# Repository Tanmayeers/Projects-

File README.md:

-----Welcome to my repository-----

About me
I am a Master's student in Embedded Systems Engineering with a strong passion for hardware design and electronics. These personal projects were created as part of my self-directed learning process to gain practical experience and refine my skills in PCB design and embedded systems development.

All the porjects are created using KiCad 8

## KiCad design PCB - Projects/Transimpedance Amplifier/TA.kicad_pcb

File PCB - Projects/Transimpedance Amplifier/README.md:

Transimpedance Amplifier with Photodiodes

Specifications:
1. Operting Voltage: 9V
2. Operating Current: 200mA
3. Output Voltage Swing: 6.5V
4. 3dB - Bandwidth: 100 ± 10 Hz
5. Noise: 5.406mVrms

Components used:
1. Double operational amplifier - LMC 6482 N
2. Precision Virtual Ground - TLE 2425
3. Photodiodes: SFH 229, BPW 21
4. 9V-Battery, Connectors, R, C

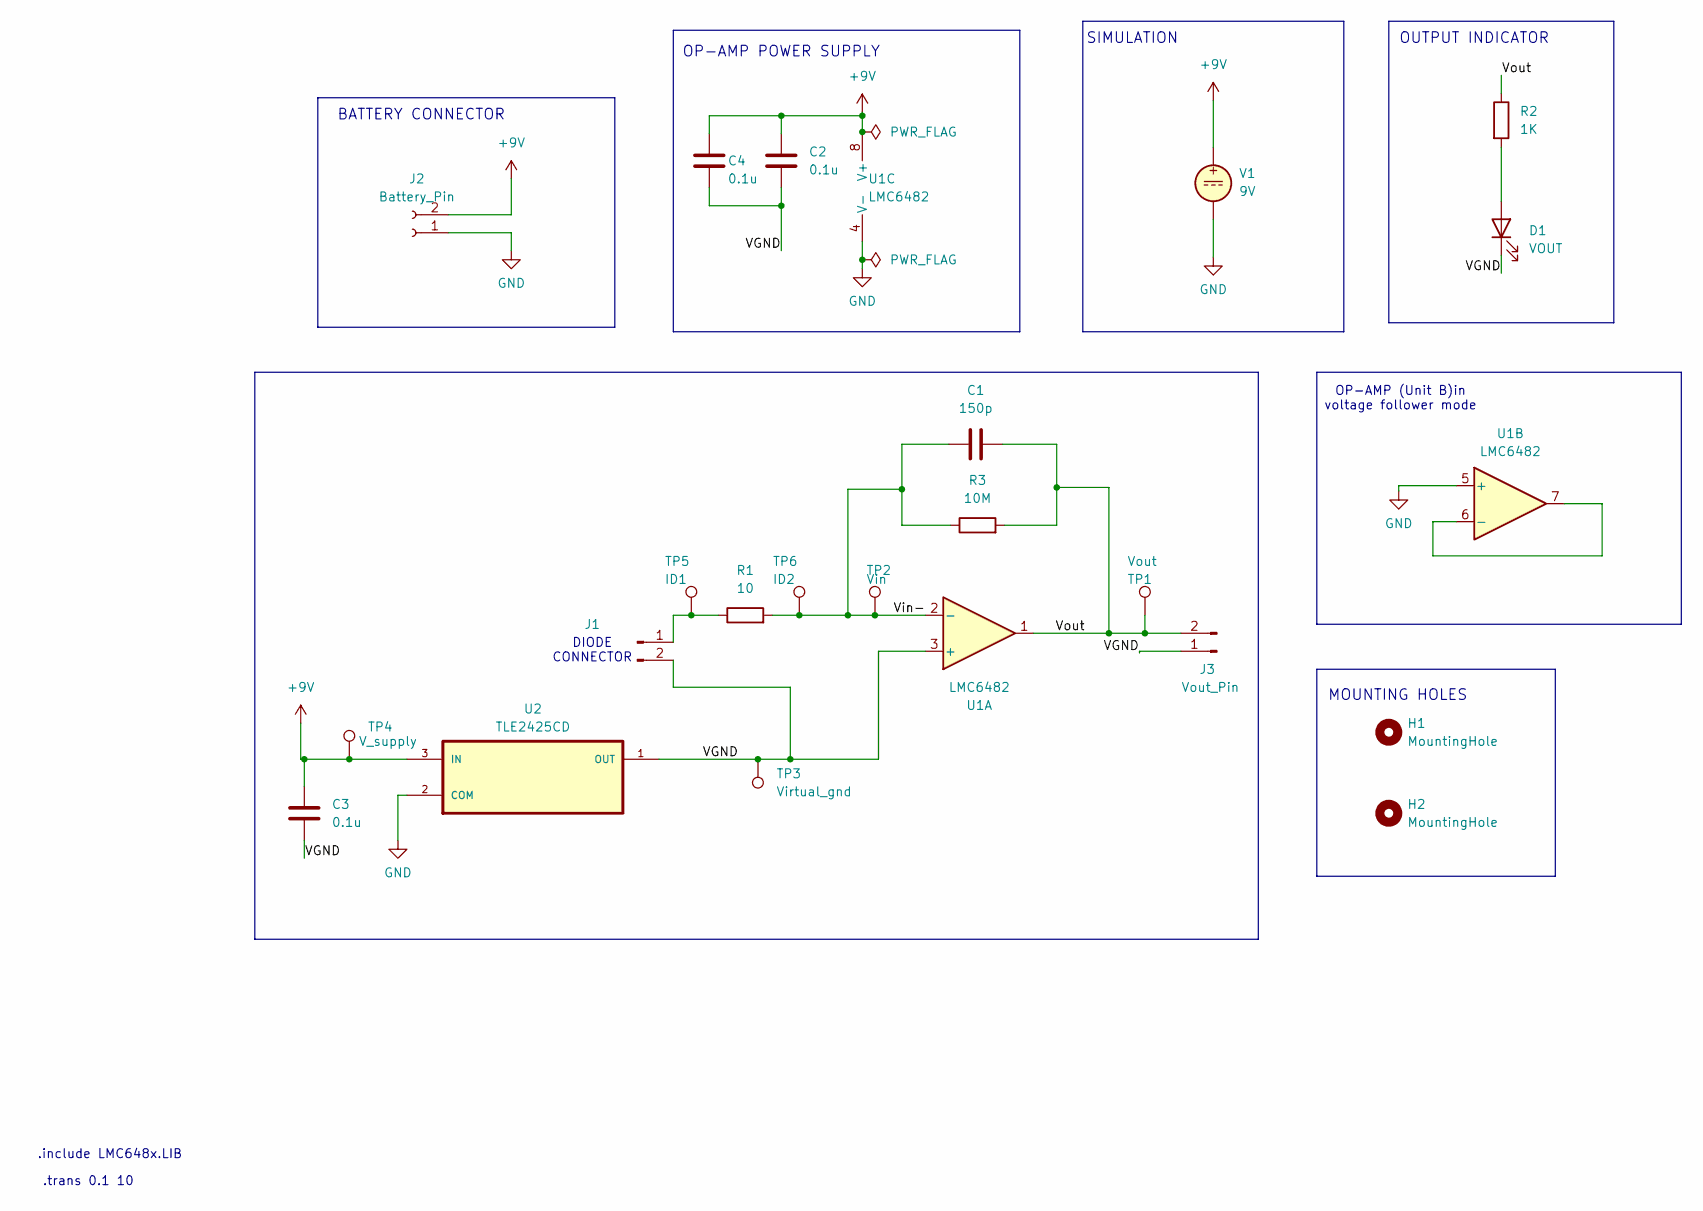
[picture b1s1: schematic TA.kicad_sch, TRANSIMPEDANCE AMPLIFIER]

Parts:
C1: 150p; C_0603_1608Metric_Pad1.08x0.95mm_HandSolder
C2, C3, C4: 0.1u; C_0603_1608Metric_Pad1.08x0.95mm_HandSolder
D1: VOUT; LED_0603_1608Metric_Pad1.05x0.95mm_HandSolder
H1, H2: MountingHole; MountingHole_4.3mm_M4_DIN965
J1: Diode_Pin; PinHeader_1x02_P2.54mm_Vertical
J2: Battery_Pin; PinHeader_1x02_P2.54mm_Vertical
J3: Vout_Pin; PinHeader_1x02_P2.54mm_Vertical
R1: 10; R_0603_1608Metric_Pad0.98x0.95mm_HandSolder
R2: 1K; R_0603_1608Metric_Pad0.98x0.95mm_HandSolder
R3: 10M; R_0805_2012Metric_Pad1.20x1.40mm_HandSolder
TP1: Vout; PinHeader_1x01_P2.54mm_Vertical
TP2: Vin; PinHeader_1x01_P2.54mm_Vertical
TP3: Virtual_gnd; PinHeader_1x01_P2.54mm_Vertical
TP4: V_supply; PinHeader_1x01_P2.54mm_Vertical
TP5: ID1; TestPoint_Pad_1.0x1.0mm
TP6: ID2; TestPoint_Pad_1.0x1.0mm
U1: LMC6482; SOIC127P599X175-8N
U2: TLE2425CD; SOIC127P599X175-8N
V1: 9V

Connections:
+9V: C2.1, C3.2, C4.1, J2.2, TP4.1, U1.8 (V+), U2.3 (IN), V1.1
/VGND: C2.2, C3.1, C4.2, D1.1 (K), J1.2, J3.1, TP3.1, U1.3 (+), U2.1 (OUT)
/Vin-: C1.1, R1.2, R3.1, TP2.1, TP6.1, U1.2 (-)
/Vout: C1.2, J3.2, R2.1, R3.2, TP1.1, U1.1
GND: J2.1, U1.4 (V-), U1.5 (+), U2.2 (COM), V1.2
unnamed: D1.2 (A), R2.2
unnamed: J1.1, R1.1, TP5.1
unnamed: U1.6 (-), U1.7

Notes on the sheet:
OP-AMP POWER SUPPLY
.include LMC648x.LIB
SIMULATION
MOUNTING HOLES
.trans 0.1 10
OP-AMP (Unit B)in voltage follower mode
DIODE CONNECTOR
OUTPUT INDICATOR
BATTERY CONNECTOR

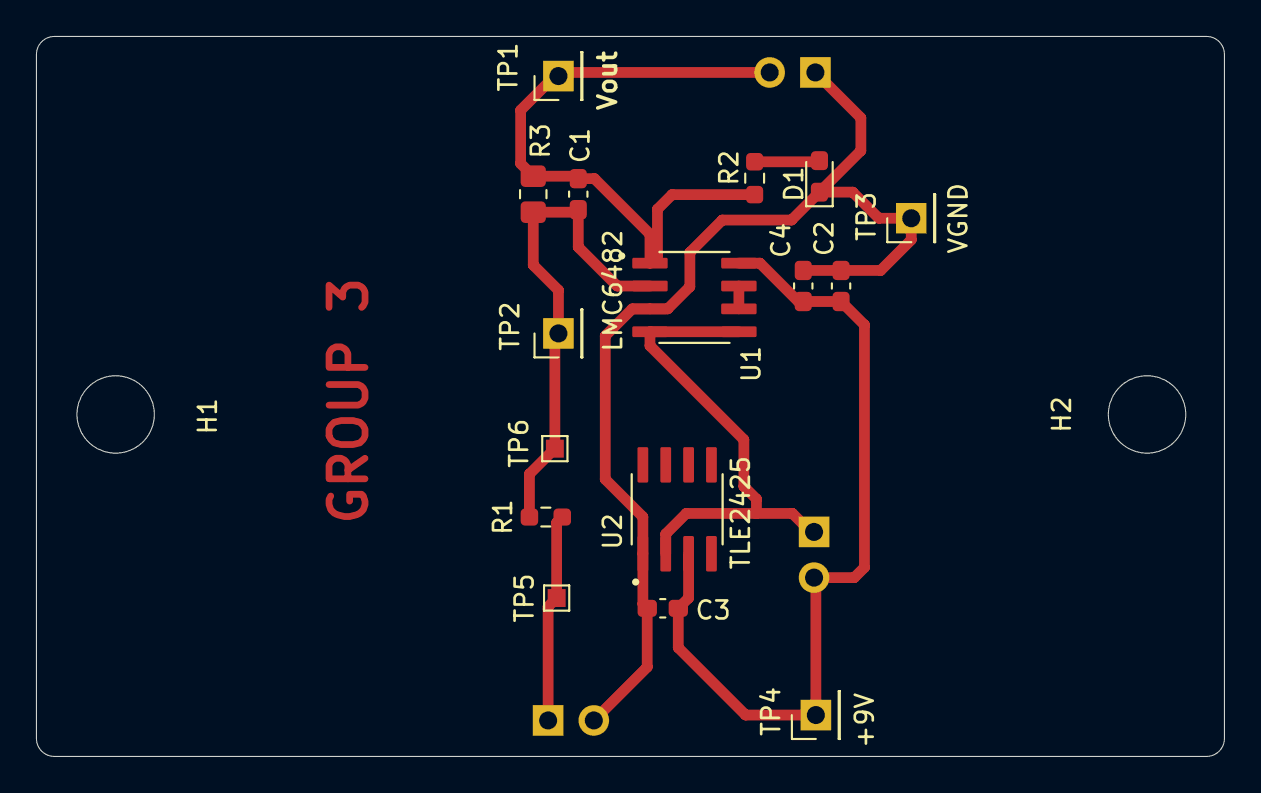
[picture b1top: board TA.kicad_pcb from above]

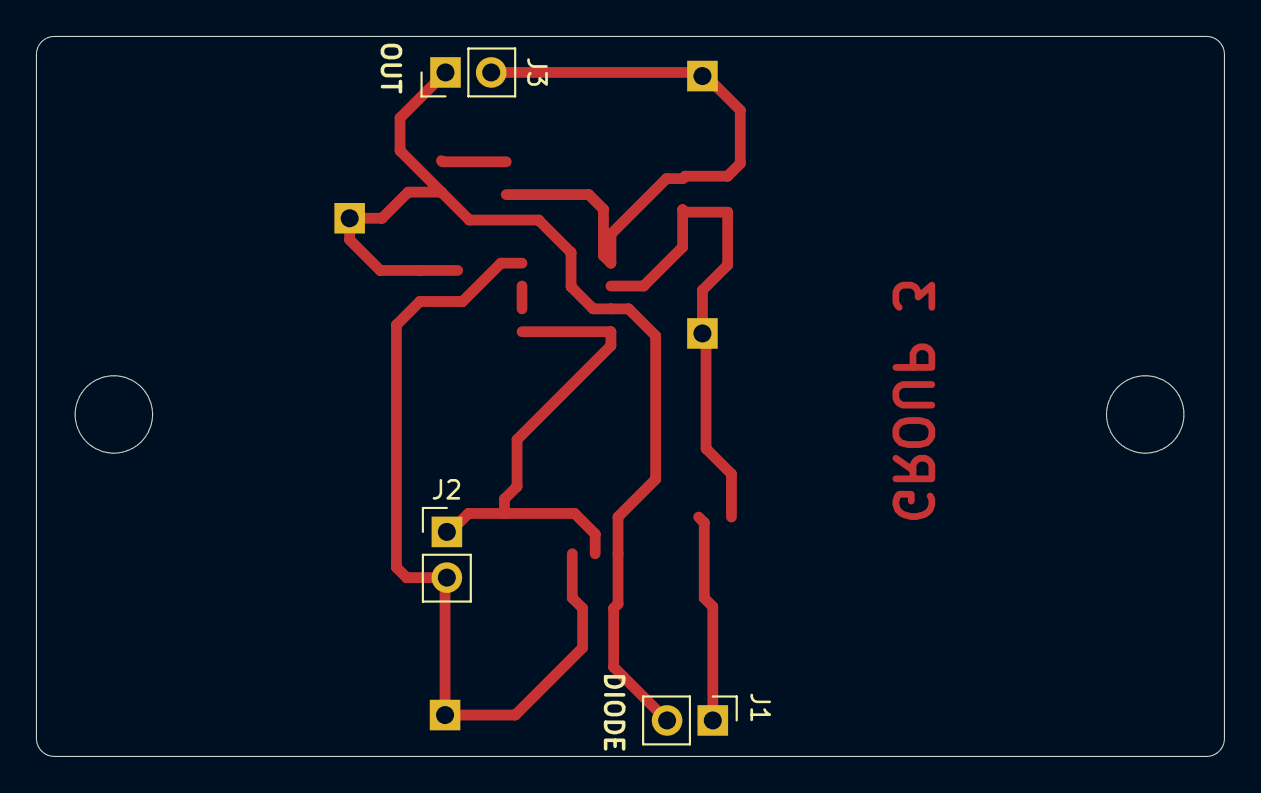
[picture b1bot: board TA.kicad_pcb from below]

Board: 2 copper layers, 66.0 x 40.0 mm, 21 parts (3 on the bottom side), 8 nets.

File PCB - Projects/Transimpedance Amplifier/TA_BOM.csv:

"Id";"Designator";"Footprint";"Quantity";"Designation";"Supplier and ref";
1;"U1";"SOIC127P599X175-8N";1;"LMC6482";;;
2;"R1";"R_0603_1608Metric_Pad0.98x0.95mm_HandSolder";1;"10";;;
3;"R2";"R_0603_1608Metric_Pad0.98x0.95mm_HandSolder";1;"1K";;;
4;"C4,C2,C3";"C_0603_1608Metric_Pad1.08x0.95mm_HandSolder";3;"0.1u";;;
5;"TP3";"PinHeader_1x01_P2.54mm_Vertical";1;"Virtual_gnd";;;
6;"C1";"C_0603_1608Metric_Pad1.08x0.95mm_HandSolder";1;"150p";;;
7;"D1";"LED_0603_1608Metric_Pad1.05x0.95mm_HandSolder";1;"VOUT";;;
8;"TP6";"TestPoint_Pad_1.0x1.0mm";1;"ID2";;;
9;"TP5";"TestPoint_Pad_1.0x1.0mm";1;"ID1";;;
10;"TP1";"PinHeader_1x01_P2.54mm_Vertical";1;"Vout";;;
11;"R3";"R_0805_2012Metric_Pad1.20x1.40mm_HandSolder";1;"10M";;;
12;"TP4";"PinHeader_1x01_P2.54mm_Vertical";1;"V_supply";;;
13;"U2";"SOIC127P599X175-8N";1;"TLE2425CD";;;
14;"TP2";"PinHeader_1x01_P2.54mm_Vertical";1;"Vin";;;
15;"J2";"PinHeader_1x02_P2.54mm_Vertical";1;"Battery_Pin";;;
16;"J1";"PinHeader_1x02_P2.54mm_Vertical";1;"Diode_Pin";;;
17;"J3";"PinHeader_1x02_P2.54mm_Vertical";1;"Vout_Pin";;;

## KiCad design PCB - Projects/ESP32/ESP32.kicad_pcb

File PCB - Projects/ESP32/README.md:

ESP32 Developmental Board

This repository contains the schematic for a custom ESP32 development board. 
The board is a 4-Layer design

Features
1. QWI2C connector for I2C devices
2. Si7021 - I2C humidity and temperature sensor
3. RGB LED with a button
4. CP2104 - USB to serial UART and on-board programmmer
5. Power relay
6. Interface for LED strips, 4 level converted outputs
7. Fused power supply available on scew terminals
8. 3.2mm mounting holes (4)

Schematic: Created independently by following the circuit from the github repository: mortens-lab/iot-thing
Layout: the PCB layout is fully original and created from scratch using KiCad
This project was developed as a personal learning exercise.

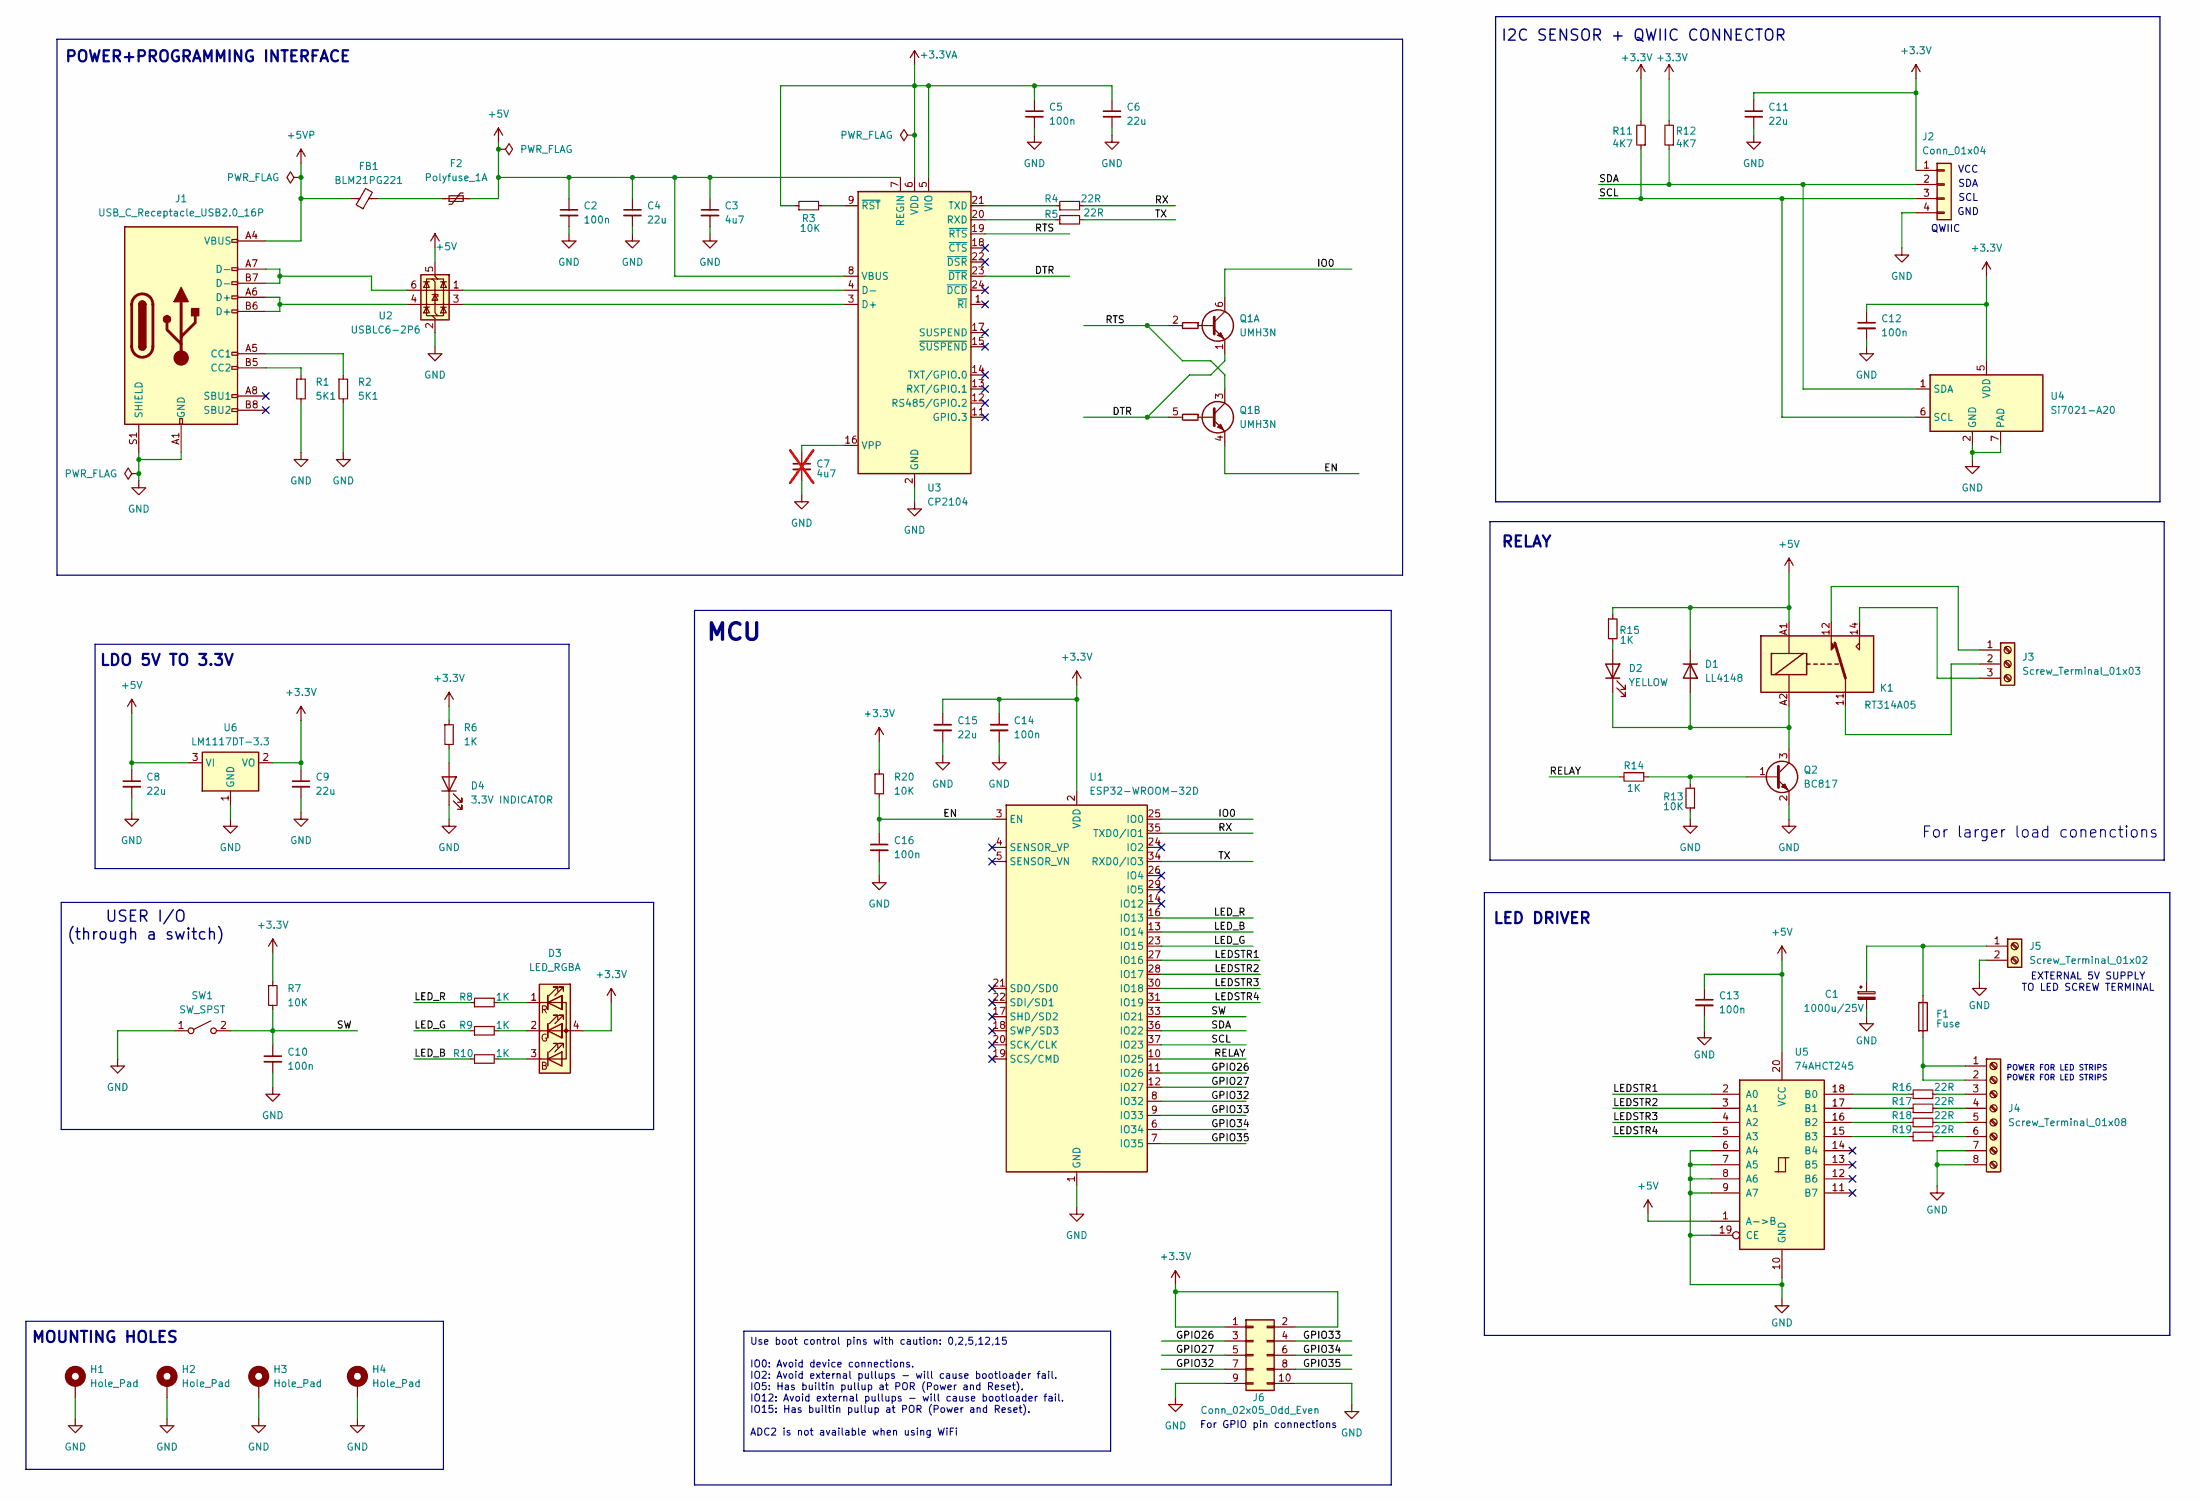
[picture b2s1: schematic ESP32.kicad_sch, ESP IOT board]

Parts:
C1: 1000u/25V; CP_Radial_D10.0mm_P5.00mm
C2, C5, C10, C12, C13, C14, C16: 100n; C_0402_1005Metric
C3: 4u7; C_0805_2012Metric
C4, C6, C8, C9, C11, C15: 22u; C_0805_2012Metric
C7: 4u7; C_0805_2012Metric; not fitted
D1: LL4148; D_MiniMELF
D2: YELLOW; LED_0603_1608Metric
D3: LED_RGBA; LED_RGB_Wuerth-PLCC4_3.2x2.8mm_150141M173100
D4: 3.3V INDICATOR; LED_0603_1608Metric
F1: Fuse; Fuse_Littelfuse-LVR200
F2: Polyfuse_1A; Fuse_Bourns_MF-RG300
FB1: BLM21PG221; L_0603_1608Metric
H1, H2, H3, H4: Hole_Pad; MountingHole_3.2mm_M3_Pad_Via
J1: USB_C_Receptacle_USB2.0_16P; USB_C_Receptacle_HRO_TYPE-C-31-M-12
J2: Conn_01x04; JST_SH_SM04B-SRSS-TB_1x04-1MP_P1.00mm_Horizontal
J3: Screw_Terminal_01x03; TerminalBlock_Phoenix_MKDS-3-3-5.08_1x03_P5.08mm_Horizontal
J4: Screw_Terminal_01x08; TerminalBlock_Phoenix_MKDS-1,5-8_1x08_P5.00mm_Horizontal
J5: Screw_Terminal_01x02; TerminalBlock_Phoenix_MKDS-1,5-2-5.08_1x02_P5.08mm_Horizont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
J6: Conn_02x05_Odd_Even; PinHeader_2x05_P2.54mm_Vertical
K1: RT314A05; Relay_SPDT_Schrack-RT1-16A-FormC_RM5mm
Q1: UMH3N; SOT-363_SC-70-6
Q2: BC817; SOT-23
R1, R2: 5K1; R_0402_1005Metric
R3, R7, R13, R20: 10K; R_0402_1005Metric
R4, R5, R16, R17, R18, R19: 22R; R_0402_1005Metric
R6, R8, R9, R10, R14, R15: 1K; R_0402_1005Metric
R11, R12: 4K7; R_0402_1005Metric
SW1: SW_SPST; SW_SPST_PTS810
U1: ESP32-WROOM-32D
U2: USBLC6-2P6; SOT-666
U3: CP2104; QFN-24-1EP_4x4mm_P0.5mm_EP2.6x2.6mm
U4: Si7021-A20; DFN-6-1EP_3x3mm_P1mm_EP1.5x2.4mm
U5: 74AHCT245; DIP-20_W7.62mm
U6: LM1117DT-3.3; TO-252-3_TabPin2

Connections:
+3.3V: C9.1, C11.1, C12.1, C14.1, C15.1, D3.4 (A), J2.1, J6.1, J6.2, R6.1, R7.1, R11.2, R12.2, R20.1, U1.2 (VDD), U4.5 (VDD), U6.2 (VO)
+3.3VA: C5.1, C6.1, R3.1, U3.5 (VIO), U3.6 (VDD)
+5V: C2.1, C3.1, C4.1, C8.1, C13.1, D1.1 (K), F2.2, K1.A1, R15.1, U2.5 (VBUS), U3.7 (REGIN), U3.8 (VBUS), U5.1 (A->B), U5.20 (VCC), U6.3 (VI)
+5VP: FB1.1, J1.A4 (VBUS), J1.A9 (VBUS), J1.B4 (VBUS), J1.B9 (VBUS)
/DTR: Q1.1 (E1), Q1.5 (B2), U3.23 (~DTR)
/EN: C16.1, Q1.4 (E2), R20.2, U1.3 (EN)
/GPIO26: J6.3, U1.11 (IO26)
/GPIO27: J6.5, U1.12 (IO27)
/GPIO32: J6.7, U1.8 (IO32)
/GPIO33: J6.4, U1.9 (IO33)
/GPIO34: J6.6, U1.6 (IO34)
/GPIO35: J6.8, U1.7 (IO35)
/IO0: Q1.6 (C1), U1.25 (IO0)
/LEDSTR1: U1.27 (IO16), U5.2 (A0)
/LEDSTR2: U1.28 (IO17), U5.3 (A1)
/LEDSTR3: U1.30 (IO18), U5.4 (A2)
/LEDSTR4: U1.31 (IO19), U5.5 (A3)
/LED_B: R10.1, U1.13 (IO14)
/LED_G: R9.1, U1.23 (IO15)
/LED_R: R8.1, U1.16 (IO13)
/RELAY: R14.2, U1.10 (IO25)
/RTS: Q1.2 (B1), Q1.3 (C2), U3.19 (~RTS)
/RX: R4.2, U1.35 (TXD0/IO1)
/SCL: J2.3, R11.1, U1.37 (IO23), U4.6 (SCL)
/SDA: J2.2, R12.1, U1.36 (IO22), U4.1 (SDA)
/SW: C10.1, R7.2, SW1.2 (B), U1.33 (IO21)
/TX: R5.2, U1.34 (RXD0/IO3)
GND: C1.2, C2.2, C3.2, C4.2, C5.2, C6.2, C7.2, C8.2, C9.2, C10.2, C11.2, C12.2, C13.2, C14.2, C15.2, C16.2, D4.1 (K), H1.1, H2.1, H3.1, H4.1, J1.A1 (GND), J1.A12 (GND), J1.B1 (GND), J1.B12 (GND), J1.S1 (SHIELD), J2.4, J4.7, J4.8, J5.2, J6.9, J6.10, Q2.2 (E), R1.2, R2.2, R13.1, SW1.1 (A), U1.1 (GND), U1.15 (GND), U1.38 (GND), U1.39 (GND), U2.2 (GND), U3.2 (GND), U3.25 (GND), U4.2 (GND), U4.7 (PAD), U5.6 (A4), U5.7 (A5), U5.8 (A6), U5.9 (A7), U5.10 (GND), U5.19 (CE), U6.1 (GND)
unnamed: D1.2 (A), D2.1 (K), K1.A2, Q2.3 (C)
unnamed: D2.2 (A), R15.2
unnamed: D3.3 (BK), R10.2
unnamed: D3.2 (GK), R9.2
unnamed: D3.1 (RK), R8.2
unnamed: D4.2 (A), R6.2
unnamed: F2.1, FB1.2
unnamed: J1.A5 (CC1), R2.1
unnamed: J1.B5 (CC2), R1.1
unnamed: J1.A6 (D+), J1.B6 (D+), U2.4 (I/O2)
unnamed: J1.A7 (D-), J1.B7 (D-), U2.6 (I/O1)
unnamed: J3.1, K1.12
unnamed: J3.2, K1.11
unnamed: J3.3, K1.14
unnamed: F1.2, J4.1, J4.2
unnamed: J4.3, R16.2
unnamed: J4.4, R17.2
unnamed: J4.5, R18.2
unnamed: J4.6, R19.2
unnamed: C1.1, F1.1, J5.1
unnamed: Q2.1 (B), R13.2, R14.1
unnamed: U2.3 (I/O2), U3.3 (D+)
unnamed: U2.1 (I/O1), U3.4 (D-)
unnamed: R5.1, U3.20 (RXD)
unnamed: R4.1, U3.21 (TXD)
unnamed: C7.1, U3.16 (VPP)
unnamed: R3.2, U3.9 (~RST)
unnamed: R16.1, U5.18 (B0)
unnamed: R17.1, U5.17 (B1)
unnamed: R18.1, U5.16 (B2)
unnamed: R19.1, U5.15 (B3)

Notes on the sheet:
Use boot control pins with caution: 0,2,5,12,15 IO0: Avoid device connections. IO2: Avoid external pullups - will cause bootloader fail. IO5: Has builtin pullup at POR (Power and Reset). IO12: Avoid external pullups - will cause bootloader fail. IO15: Has builtin pullup at POR (Power and Reset). AD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
POWER FOR LED STRIPS
GND
LED DRIVER
For GPIO pin connections
EXTERNAL 5V SUPPLY TO LED SCREW TERMINAL
VCC
I2C SENSOR + QWIIC CONNECTOR
LDO 5V TO 3.3V
SCL
RELAY
SDA
POWER+PROGRAMMING INTERFACE
MOUNTING HOLES
For larger load conenctions
USER I/O (through a switch)
MCU
QWIIC

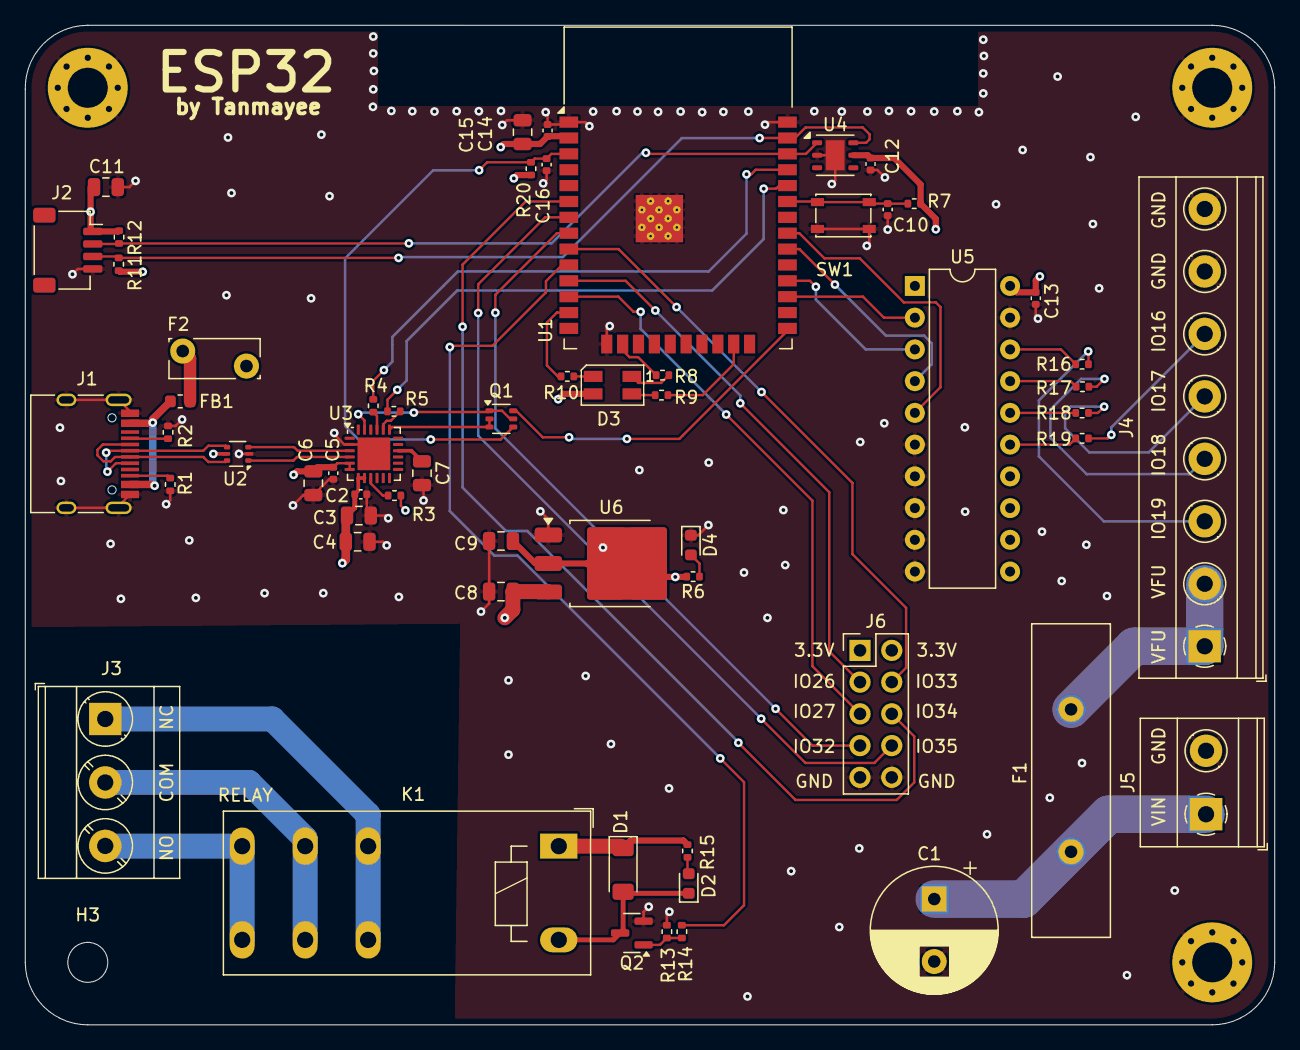
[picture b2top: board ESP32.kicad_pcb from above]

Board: 4 copper layers, 100.0 x 80.0 mm, 63 parts (0 on the bottom side), 59 nets.

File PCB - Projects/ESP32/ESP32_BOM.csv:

"Id";"Designator";"Footprint";"Quantity";"Designation";"Supplier and ref";
1;"F2";"Fuse_Bourns_MF-RG300";1;"Polyfuse_1A";;;
2;"U3";"QFN-24-1EP_4x4mm_P0.5mm_EP2.6x2.6mm";1;"CP2104";;;
3;"D2";"LED_0603_1608Metric";1;"YELLOW";;;
4;"R11,R12";"R_0402_1005Metric";2;"4K7";;;
5;"U2";"SOT-666";1;"USBLC6-2P6";;;
6;"C9,C6,C15,C4,C11,C8";"C_0805_2012Metric";6;"22u";;;
7;"U1";"ESP32-WROOM-32D";1;"ESP32-WROOM-32D";;;
8;"F1";"Fuse_Littelfuse-LVR200";1;"Fuse";;;
9;"U6";"TO-252-3_TabPin2";1;"LM1117DT-3.3";;;
10;"R3,R7,R13,R20";"R_0402_1005Metric";4;"10K";;;
11;"C13,C12,C16,C10,C2,C14,C5";"C_0402_1005Metric";7;"100n";;;
12;"K1";"Relay_SPDT_Schrack-RT1-16A-FormC_RM5mm";1;"RT314A05";;;
13;"Q1";"SOT-363_SC-70-6";1;"UMH3N";;;
14;"C1";"CP_Radial_D10.0mm_P5.00mm";1;"1000u/25V";;;
15;"R10,R8,R6,R14,R9,R15";"R_0402_1005Metric";6;"1K";;;
16;"R4,R5,R18,R19,R17,R16";"R_0402_1005Metric";6;"22R";;;
17;"SW1";"SW_SPST_PTS810";1;"SW_SPST";;;
18;"D1";"D_MiniMELF";1;"LL4148";;;
19;"J1";"USB_C_Receptacle_HRO_TYPE-C-31-M-12";1;"USB_C_Receptacle_USB2.0_16P";;;
20;"U5";"DIP-20_W7.62mm";1;"74AHCT245";;;
21;"J2";"JST_SH_SM04B-SRSS-TB_1x04-1MP_P1.00mm_Horizontal";1;"Conn_01x04";;;
22;"D3";"LED_RGB_Wuerth-PLCC4_3.2x2.8mm_150141M173100";1;"LED_RGBA";;;
23;"J3";"TerminalBlock_Phoenix_MKDS-3-3-5.08_1x03_P5.08mm_Horizontal";1;"Screw_Terminal_01x03";;;
24;"FB1";"L_0603_1608Metric";1;"BLM21PG221";;;
25;"C3";"C_0805_2012Metric";1;"4u7";;;
26;"J5";"TerminalBlock_Phoenix_MKDS-1,5-2-5.08_1x02_P5.08mm_Horizontal";1;"Screw_Terminal_01x02";;;
27;"Q2";"SOT-23";1;"BC817";;;
28;"R1,R2";"R_0402_1005Metric";2;"5K1";;;
29;"J4";"TerminalBlock_Phoenix_MKDS-1,5-8_1x08_P5.00mm_Horizontal";1;"Screw_Terminal_01x08";;;
30;"D4";"LED_0603_1608Metric";1;"3.3V INDICATOR";;;
31;"J6";"PinHeader_2x05_P2.54mm_Vertical";1;"Conn_02x05_Odd_Even";;;
32;"U4";"DFN-6-1EP_3x3mm_P1mm_EP1.5x2.4mm";1;"Si7021-A20";;;

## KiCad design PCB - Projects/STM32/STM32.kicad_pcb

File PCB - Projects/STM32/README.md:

STM32 Development Board – Custom PCB

This repository contains the schematic and PCB layout for a custom STM32-based development board. The schematic design is based on a tutorial by [Phil's Lab] (see below), but the PCB layout is fully original and created from scratch using KiCad.

Overview

The project is based on the STM32F103C8T6 microcontroller (or compatible), ideal for embedded development. It includes all essential components required to get started with STM32 programming, debugging, and I/O testing.

Features

SWD Header for flashing and debugging,
3.3V Voltage Regulator,
Reset Button,
User Button,
Status LED,
Crystal Oscillator with load capacitors and
Breakout I/O headers

Schematic source: Created independently by following the circuit by Phil's Lab
PCB Layout: Fully original layout, designed from scratch including component placement, routing, and clearance optimization.

This project was developed as a personal learning exercise.

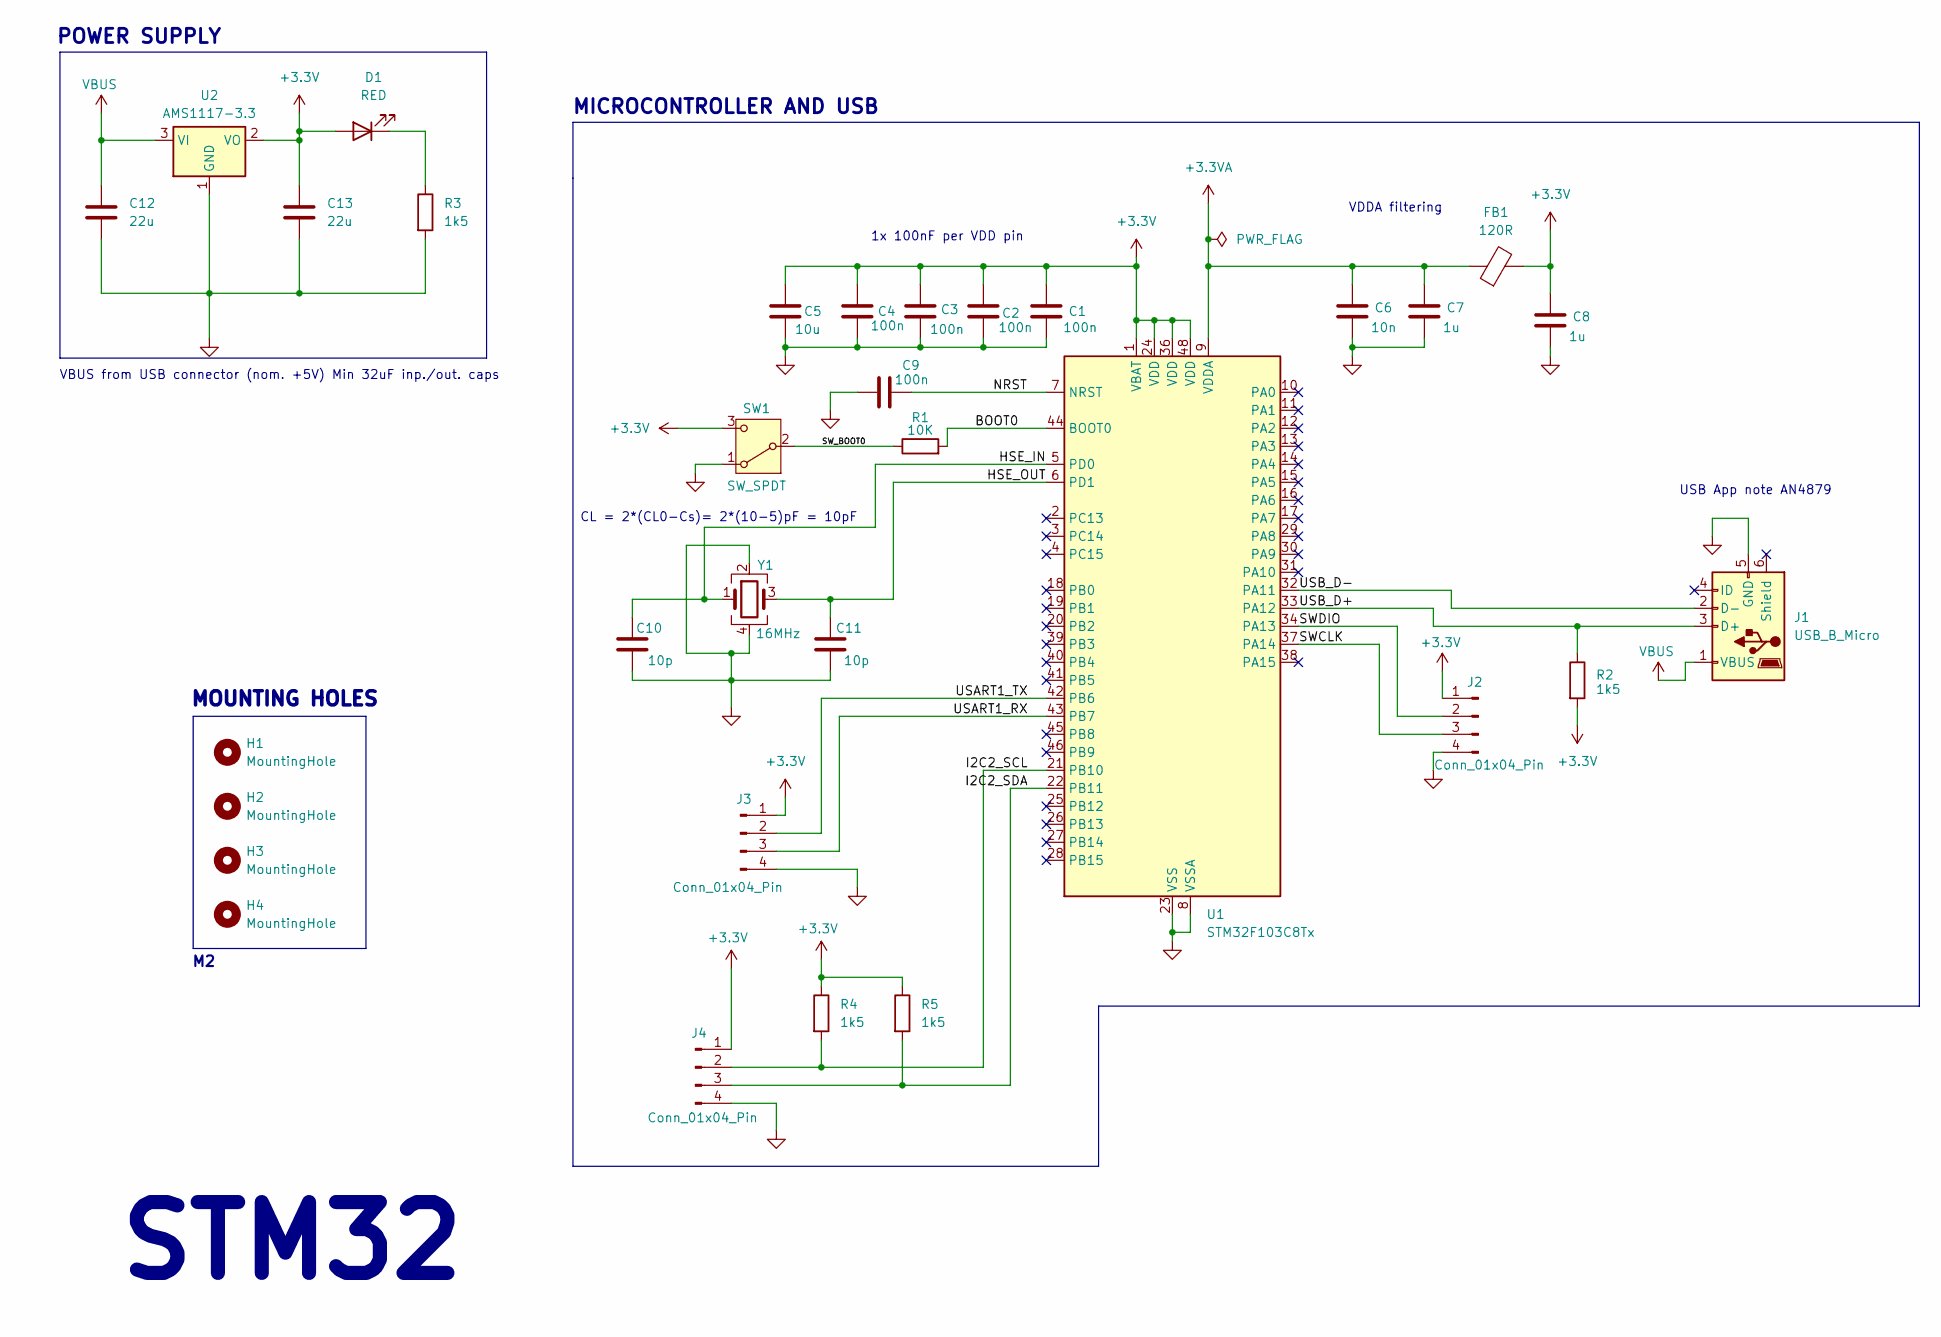
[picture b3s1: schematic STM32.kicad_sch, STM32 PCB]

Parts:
C1, C2, C3, C4, C9: 100n; C_0402_1005Metric
C5: 10u; C_0603_1608Metric
C6: 10n; C_0402_1005Metric
C7, C8: 1u; C_0402_1005Metric
C10, C11: 10p; C_0402_1005Metric
C12, C13: 22u; C_0805_2012Metric
D1: RED; LED_0603_1608Metric
FB1: 120R; L_0603_1608Metric
H1, H2, H3, H4: MountingHole; MountingHole_2.2mm_M2
J1: USB_B_Micro; USB_Micro-B_Wuerth_629105150521
J2, J3, J4: Conn_01x04_Pin; PinHeader_1x04_P2.54mm_Vertical
R1: 10K; R_0402_1005Metric
R2, R3, R4, R5: 1k5; R_0402_1005Metric
SW1: SW_SPDT; SW_SPDT_PCM12
U1: STM32F103C8Tx; LQFP-48_7x7mm_P0.5mm
U2: AMS1117-3.3; SOT-223-3_TabPin2
Y1: 16MHz; Crystal_SMD_3225-4Pin_3.2x2.5mm

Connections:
+3.3V: C1.1, C2.1, C3.1, C4.1, C5.1, C8.1, C13.2, D1.2 (A), FB1.2, J2.1, J3.1, J4.1, R2.2, R4.1, R5.1, SW1.3 (C), U1.1 (VBAT), U1.24 (VDD), U1.36 (VDD), U1.48 (VDD), U2.2 (VO)
+3.3VA: C6.1, C7.1, FB1.1, U1.9 (VDDA)
/BOOT0: R1.2, U1.44 (BOOT0)
/HSE_IN: C10.2, U1.5 (PD0), Y1.1
/HSE_OUT: C11.2, U1.6 (PD1), Y1.3
/I2C2_SCL: J4.2, R4.2, U1.21 (PB10)
/I2C2_SDA: J4.3, R5.2, U1.22 (PB11)
/NRST: C9.2, U1.7 (NRST)
/SWCLK: J2.3, U1.37 (PA14)
/SWDIO: J2.2, U1.34 (PA13)
/SW_BOOT0: R1.1, SW1.2 (B)
/USART1_RX: J3.3, U1.43 (PB7)
/USART1_TX: J3.2, U1.42 (PB6)
/USB_D+: J1.3 (D+), R2.1, U1.33 (PA12)
/USB_D-: J1.2 (D-), U1.32 (PA11)
GND: C1.2, C2.2, C3.2, C4.2, C5.2, C6.2, C7.2, C8.2, C9.1, C10.1, C11.1, C12.1, C13.1, J1.5 (GND), J2.4, J3.4, J4.4, R3.2, SW1.1 (A), U1.8 (VSSA), U1.23 (VSS), U1.35 (VSS), U1.47 (VSS), U2.1 (GND), Y1.2, Y1.4
unnamed: D1.1 (K), R3.1
VBUS: C12.2, J1.1 (VBUS), U2.3 (VI)

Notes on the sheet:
MOUNTING HOLES
VDDA filtering
STM32
USB App note AN4879
VBUS from USB connector (nom. +5V) Min 32uF inp./out. caps
CL = 2*(CL0-Cs)= 2*(10-5)pF = 10pF
1x 100nF per VDD pin
MICROCONTROLLER AND USB
POWER SUPPLY

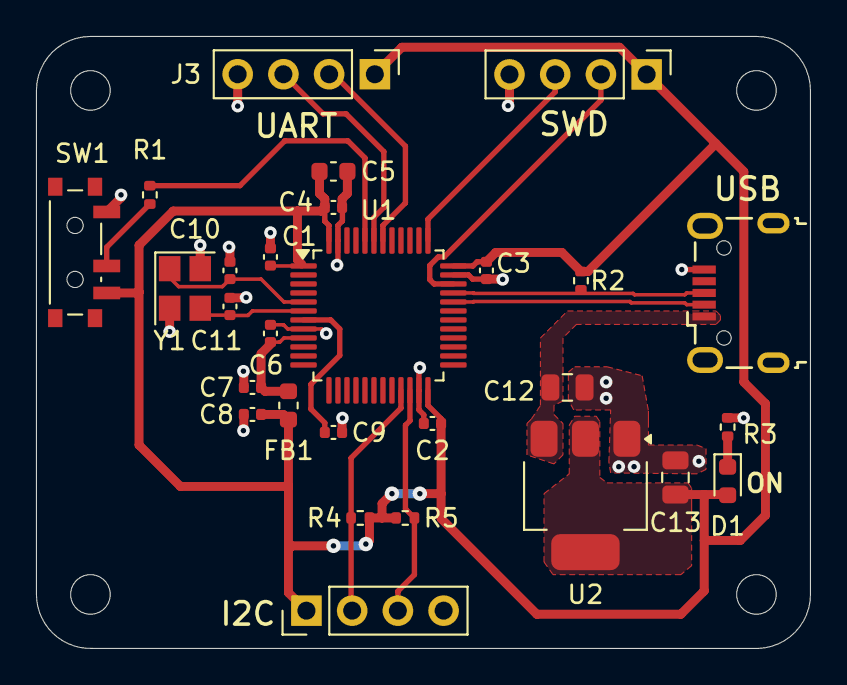
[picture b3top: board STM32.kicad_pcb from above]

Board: 2 copper layers, 43.0 x 34.0 mm, 32 parts (0 on the bottom side), 18 nets.

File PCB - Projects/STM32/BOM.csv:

"Reference","Value","Datasheet","Footprint","Qty","DNP"
"C1,C2,C3,C4,C9","100n","~","Capacitor_SMD:C_0402_1005Metric","5",""
"C5","10u","~","Capacitor_SMD:C_0603_1608Metric","1",""
"C6","10n","~","Capacitor_SMD:C_0402_1005Metric","1",""
"C7,C8","1u","~","Capacitor_SMD:C_0402_1005Metric","2",""
"C10,C11","10p","~","Capacitor_SMD:C_0402_1005Metric","2",""
"C12,C13","22u","~","Capacitor_SMD:C_0805_2012Metric","2",""
"D1","RED","~","LED_SMD:LED_0603_1608Metric","1",""
"FB1","120R","~","Inductor_SMD:L_0603_1608Metric","1",""
"J1","USB_B_Micro","~","Connector_USB:USB_Micro-B_Wuerth_629105150521","1",""
"J2,J3,J4","Conn_01x04_Pin","~","Connector_PinHeader_2.54mm:PinHeader_1x04_P2.54mm_Vertical","3",""
"R1","10K","~","Resistor_SMD:R_0402_1005Metric","1",""
"R2,R3,R4,R5","1k5","~","Resistor_SMD:R_0402_1005Metric","4",""
"SW1","SW_SPDT","~","Button_Switch_SMD:SW_SPDT_PCM12","1",""
"U1","STM32F103C8Tx","https://www.st.com/resource/en/datasheet/stm32f103c8.pdf","Package_QFP:LQFP-48_7x7mm_P0.5mm","1",""
"U2","AMS1117-3.3","http://www.advanced-monolithic.com/pdf/ds1117.pdf","Package_TO_SOT_SMD:SOT-223-3_TabPin2","1",""
"Y1","16MHz","~","Crystal:Crystal_SMD_3225-4Pin_3.2x2.5mm","1",""
